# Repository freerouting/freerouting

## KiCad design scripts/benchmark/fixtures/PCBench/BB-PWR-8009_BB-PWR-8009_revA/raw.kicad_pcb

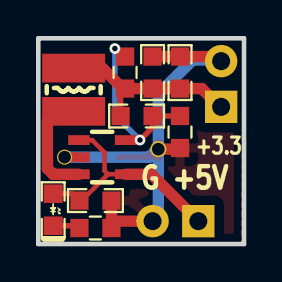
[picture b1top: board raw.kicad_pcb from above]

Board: 2 copper layers, 11.4 x 11.4 mm, 14 parts (0 on the bottom side), 6 nets.

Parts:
C1, C3, C4: 22uF/6.3V; C_0603
C2: 22pF; C_0603
D1: LED_RED_0603; LED_0603_KA
L1: 2.2uH/1.5A/JCR<0.1R/CD32; CD32
P1, P2: HN1x2; HN1x2_Jumper
R1: 4.99K 1%; R_0603_DWS
R2: 1.1K 1%; R_0603_DWS
R3: 2.2K; R_0603_DWS
Ref**: Val**; via_09_07
Ref**#2: Val**; via_09_07
U1: SY8009AAAC(SOT23-5); SOT-23-5

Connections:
GND: C1.2, C3.2, C4.2, P1.2, P2.2, R2.2, R3.1, Ref**.0, Ref**#2.0, U1.2
unnamed: C1.1, D1.2, P1.1, U1.1, U1.4
unnamed: C2.1, C3.1, C4.1, L1.2, P2.1, R1.1
unnamed: C2.2, R1.2, R2.1, U1.5
unnamed: D1.1, R3.2
unnamed: L1.1, U1.3

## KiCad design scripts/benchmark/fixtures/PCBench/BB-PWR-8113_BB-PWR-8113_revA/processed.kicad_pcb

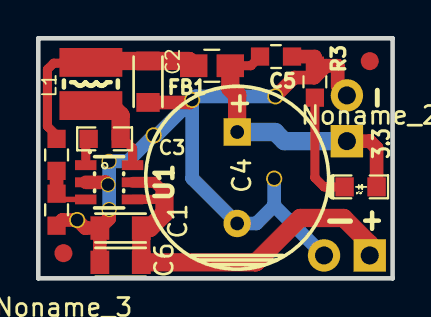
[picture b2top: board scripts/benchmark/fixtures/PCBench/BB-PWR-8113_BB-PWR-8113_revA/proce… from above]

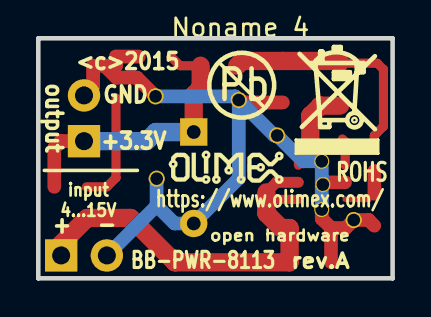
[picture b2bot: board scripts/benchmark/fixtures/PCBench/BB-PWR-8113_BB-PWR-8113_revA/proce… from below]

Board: 2 copper layers, 19.7 x 13.3 mm, 28 parts (3 on the bottom side), 8 nets.

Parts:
C1, C6: 2.2uF/50V; R_0805
C2: 22uF/6.3V; R_0805
C3: 100nF; C_0603
C4: 1000uF 6.3V Low ESR; CPOL_200mils_R10mm
C5: 100nF; C_0603_DWS
D1: LED_RED_0603; LED_0603_KA
FB1: FB0805-2A; L0805_5MIL_DWS
L1: 4.7uH/1.5A/JCR<0.1R/CD32; CD32
Noname_1: LOGO_RECYCLEBIN_1
Noname_2, Noname_3: Fiducial1x3_transp
Noname_4: LOGO_PBFREE
Noname_5: LOGO_OLIMEX_80
P1, P2: HN1x2; HN1x2_Jumper
R1: 100K 1%; R_0603_DWS
R2: 22.1K 1%; R_0603_DWS
R3: 2.2K; R_0603_DWS
Ref**: Val**; via_09_07
Ref**_2, Ref**_3, Ref**_4, Ref**_5, Ref**_6, Ref**_7, Ref**_8: Val**; via_09_07
U1: SY8120B1; SOT23-6

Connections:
GND: C1.2, C2.2, C4.2, C5.2, C6.2, P1.2, P2.2, R2.2, R3.1, Ref**.0, Ref**_2.0, Ref**_3.0, Ref**_4.0, Ref**_5.0, Ref**_6.0, Ref**_7.0, Ref**_8.0, U1.2
unnamed: C1.1, C6.1, P1.1, U1.4, U1.5
unnamed: C2.1, FB1.1, L1.2, R1.1
unnamed: C3.1, L1.1, U1.6
unnamed: C3.2, U1.1
unnamed: C4.1, C5.1, D1.2, FB1.2, P2.1
unnamed: D1.1, R3.2
unnamed: R1.2, R2.1, U1.3

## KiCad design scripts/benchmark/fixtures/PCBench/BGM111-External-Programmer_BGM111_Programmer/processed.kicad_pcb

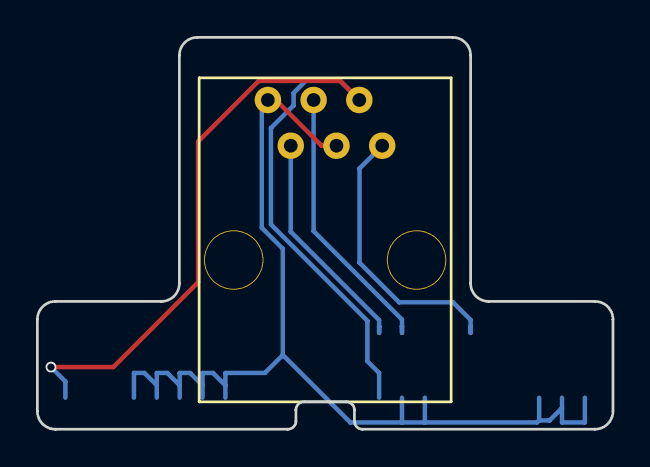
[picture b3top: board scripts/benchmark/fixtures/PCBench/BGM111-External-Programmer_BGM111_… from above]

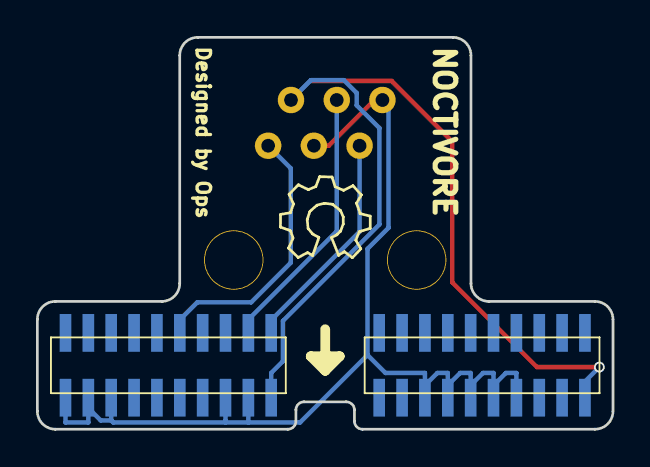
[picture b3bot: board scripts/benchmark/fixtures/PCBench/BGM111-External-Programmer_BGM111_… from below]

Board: 2 copper layers, 32.0 x 21.8 mm, 3 parts (2 on the bottom side), 5 nets.

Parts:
J1: FCI_RJ12; RJ12
P1: Debug Connector; Pin_Header_Straight_2X20_Pitch_1.27mm
P2: Simplicity Connector; Pin_Header_Straight_2X20_Pitch_1.27mm

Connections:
+3V3: J1.5, P1.2, P2.2
/RESET: J1.6, P1.9
/SWCLK: J1.3, P1.3
/SWDIO: J1.2, P1.1
GND: J1.1, J1.4, P1.4, P1.6, P1.16, P1.18, P1.20, P2.8, P2.10, P2.12, P2.14, P2.16
